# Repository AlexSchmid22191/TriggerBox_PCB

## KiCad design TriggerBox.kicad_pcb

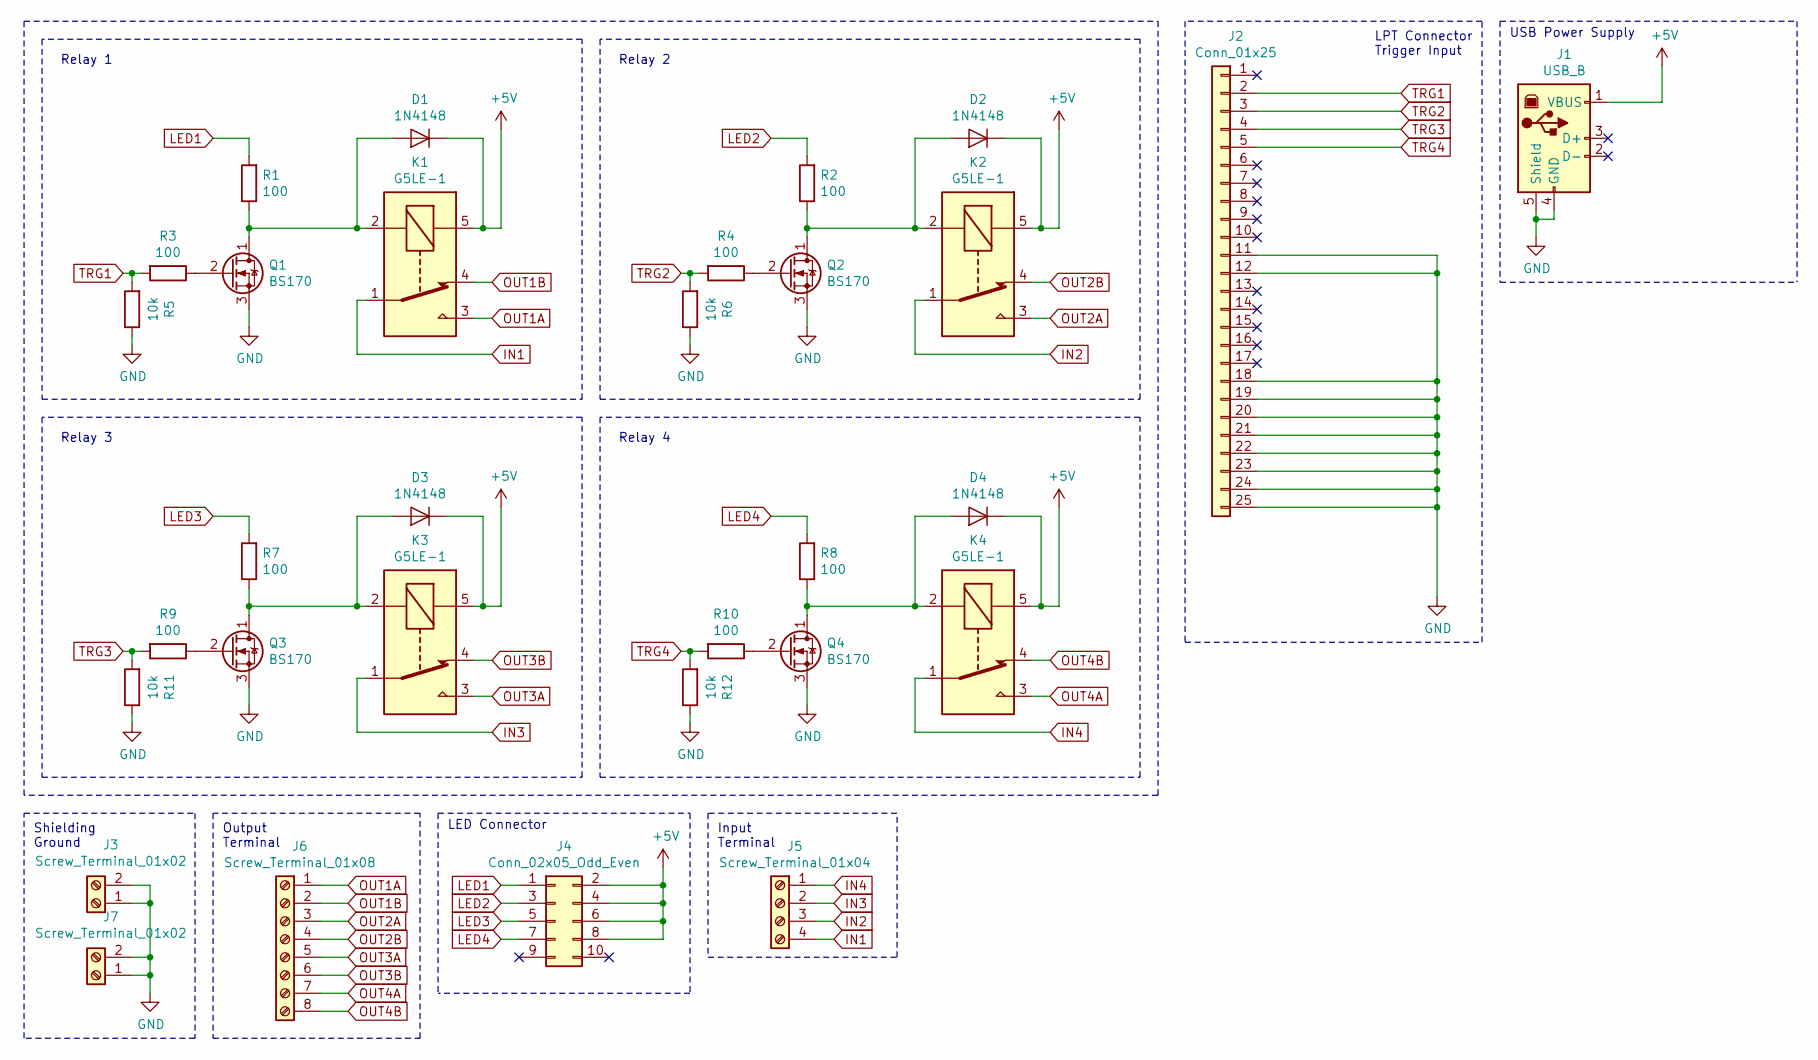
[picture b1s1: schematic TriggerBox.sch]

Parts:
D1, D2, D3, D4: 1N4148; D_DO-35_SOD27_P10.16mm_Horizontal
J1: USB_B; USB_B_OST_USB-B1HSxx_Horizontal
J2: Conn_01x25; IDC_13x02
J3, J7: Screw_Terminal_01x02; RS_Screw_Term_x2
J4: Conn_02x05_Odd_Even; IDC_05x02
J5: Screw_Terminal_01x04; RS_Screw_Term_x4
J6: Screw_Terminal_01x08; RS_Screw_Term_x8
K1, K2, K3, K4: G5LE-1; Relay_SPDT_Omron-G5LE-1
Q1, Q2, Q3, Q4: BS170; TO-92_Inline
R1, R2, R3, R4, R7, R8, R9, R10: 100; R_0603_1608Metric_Pad1.05x0.95mm_HandSolder
R5, R6, R11, R12: 10k; R_0603_1608Metric_Pad1.05x0.95mm_HandSolder

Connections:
+5V: D1.1 (K), D2.1 (K), D3.1 (K), D4.1 (K), J1.1 (VBUS), J4.2, J4.4, J4.6, J4.8, K1.5, K2.5, K3.5, K4.5
GND: J1.4 (GND), J1.5 (Shield), J2.11, J2.12, J2.18, J2.19, J2.20, J2.21, J2.22, J2.23, J2.24, J2.25, J3.1, J3.2, J7.1, J7.2, Q1.3 (S), Q2.3 (S), Q3.3 (S), Q4.3 (S), R5.1, R6.1, R11.1, R12.1
IN1: J5.4, K1.1
IN2: J5.3, K2.1
IN3: J5.2, K3.1
IN4: J5.1, K4.1
LED1: J4.1, R1.2
LED2: J4.3, R2.2
LED3: J4.5, R7.2
LED4: J4.7, R8.2
unnamed: D1.2 (A), K1.2, Q1.1 (D), R1.1
unnamed: D2.2 (A), K2.2, Q2.1 (D), R2.1
unnamed: D3.2 (A), K3.2, Q3.1 (D), R7.1
unnamed: D4.2 (A), K4.2, Q4.1 (D), R8.1
unnamed: Q1.2 (G), R3.1
unnamed: Q2.2 (G), R4.1
unnamed: Q3.2 (G), R9.1
unnamed: Q4.2 (G), R10.1
OUT1A: J6.1, K1.3
OUT1B: J6.2, K1.4
OUT2A: J6.3, K2.3
OUT2B: J6.4, K2.4
OUT3A: J6.5, K3.3
OUT3B: J6.6, K3.4
OUT4A: J6.7, K4.3
OUT4B: J6.8, K4.4
TRG1: J2.2, R3.2, R5.2
TRG2: J2.3, R4.2, R6.2
TRG3: J2.4, R9.2, R11.2
TRG4: J2.5, R10.2, R12.2

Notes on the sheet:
Relay 1
Relay 3
Relay 4
Relay 2
LPT Connector Trigger Input
Output Terminal
Input Terminal
USB Power Supply
LED Connector
Shielding Ground

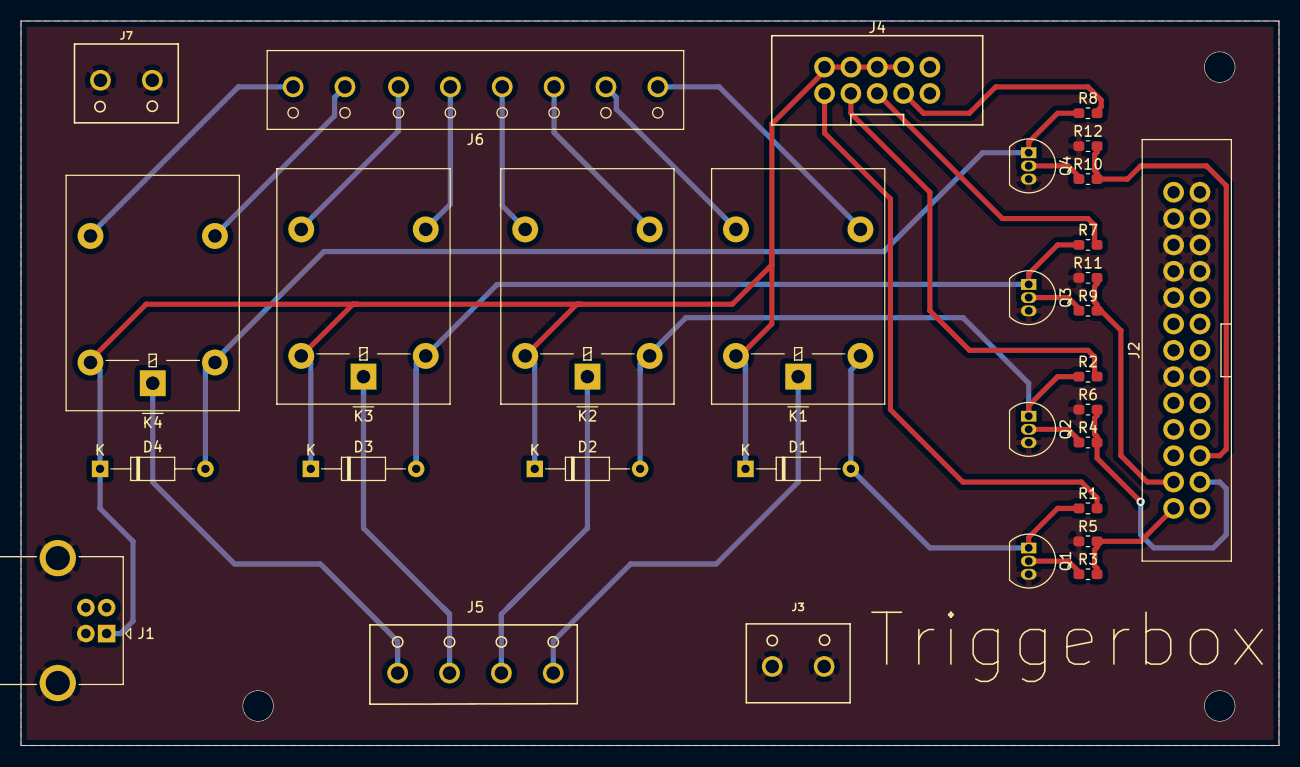
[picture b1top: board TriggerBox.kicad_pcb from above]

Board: 2 copper layers, 121.3 x 69.9 mm, 31 parts (0 on the bottom side), 30 nets.
